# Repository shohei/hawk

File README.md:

# hawk
Small ARM dev board based on ATSAMD10.
https://github.com/MalphasWats/hawk

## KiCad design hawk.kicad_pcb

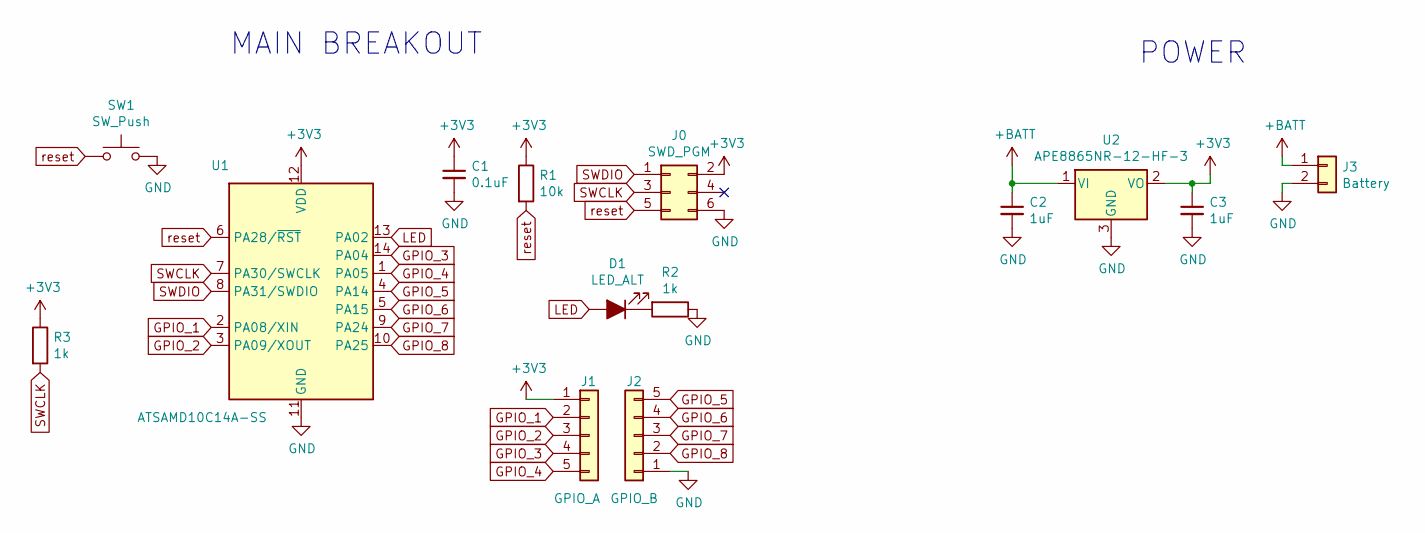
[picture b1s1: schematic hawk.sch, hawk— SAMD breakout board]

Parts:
C1: 0.1uF; C_0805_2012Metric_Pad1.15x1.40mm_HandSolder
C2, C3: 1uF; C_0805_2012Metric_Pad1.15x1.40mm_HandSolder
D1: LED_ALT; LED_0805_2012Metric_Pad1.15x1.40mm_HandSolder
J0: SWD_PGM; PinHeader_2x03_P2.54mm_Vertical
J1: GPIO_A; PinHeader_1x05_P2.54mm_Vertical
J2: GPIO_B; PinHeader_1x05_P2.54mm_Vertical
J3: Battery; PinHeader_1x02_P2.54mm_Vertical
R1: 10k; R_0805_2012Metric_Pad1.15x1.40mm_HandSolder
R2, R3: 1k; R_0805_2012Metric_Pad1.15x1.40mm_HandSolder
SW1: SW_Push; SW_PUSH_6mm
U1: ATSAMD10C14A-SS; SOIC-14_3.9x8.7mm_P1.27mm
U2: APE8865NR-12-HF-3; SOT-23

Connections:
+3V3: C1.1, C3.1, J0.2, J1.1, R1.1, R3.1, U1.12 (VDD), U2.2 (VO)
+BATT: C2.1, J3.1, U2.1 (VI)
GND: C1.2, C2.2, C3.2, J0.6, J2.1, J3.2, R2.1, SW1.2, U1.11 (GND), U2.3 (GND)
GPIO_1: J1.2, U1.2 (PA08/XIN)
GPIO_2: J1.3, U1.3 (PA09/XOUT)
GPIO_3: J1.4, U1.14 (PA04)
GPIO_4: J1.5, U1.1 (PA05)
GPIO_5: J2.5, U1.4 (PA14)
GPIO_6: J2.4, U1.5 (PA15)
GPIO_7: J2.3, U1.9 (PA24)
GPIO_8: J2.2, U1.10 (PA25)
LED: D1.2 (A), U1.13 (PA02)
unnamed: D1.1 (K), R2.2
SWCLK: J0.3, R3.2, U1.7 (PA30/SWCLK)
SWDIO: J0.1, U1.8 (PA31/SWDIO)
reset: J0.5, R1.2, SW1.1, U1.6 (PA28/~RST)

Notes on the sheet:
MAIN BREAKOUT
POWER

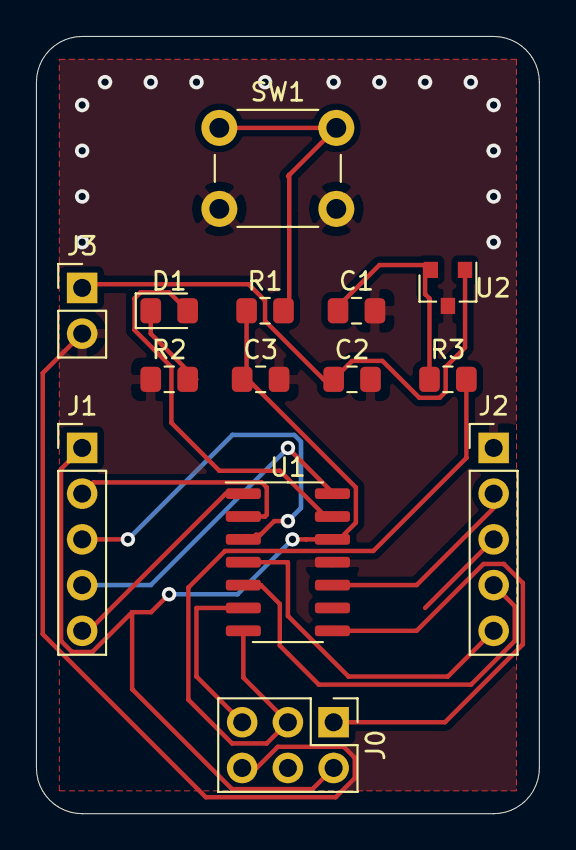
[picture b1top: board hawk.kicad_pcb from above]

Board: 2 copper layers, 27.9 x 43.2 mm, 14 parts (0 on the bottom side), 16 nets.

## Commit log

2020-10-06 add readme
